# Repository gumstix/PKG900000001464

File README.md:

# Gumstix Raspberry Pi CM4 UprevAI
## PKG900000001464 ![][thumbnail]

The **Gumstix Raspberry Pi CM4 UprevAI** replaces the CM3 compute module on compatible carrier boards, adding a CM4 connector and Google Coral TPU chip.
Accelerate your hardware and migrate it into the field of **Edge AI** without revising your design.

__Features Include__:
* Raspberry Pi CM3 compatible SODIMM edge connection
* Power indicator LED
* Google Coral G313-06329-00 TPU

__Links:__
* [AutoDoc Datasheet][autodoc]
* [Specifications][spec]
* [Store Page][store]
* [Schematics and Layout][hardware]

[thumbnail]: https://d3iwea566ns1n1.cloudfront.net/images/product/40edad650346ab020427c20a98565f45689e575a.png
[autodoc]: PKG900000001464_AutoDoc.pdf
[spec]: PKG900000001464_SpecSheet.pdf
[store]: https://store.gumstix.com/cm4-uprev-ai/
[hardware]: hardware/hardware.md
[firmware]: firmware/firmware.md

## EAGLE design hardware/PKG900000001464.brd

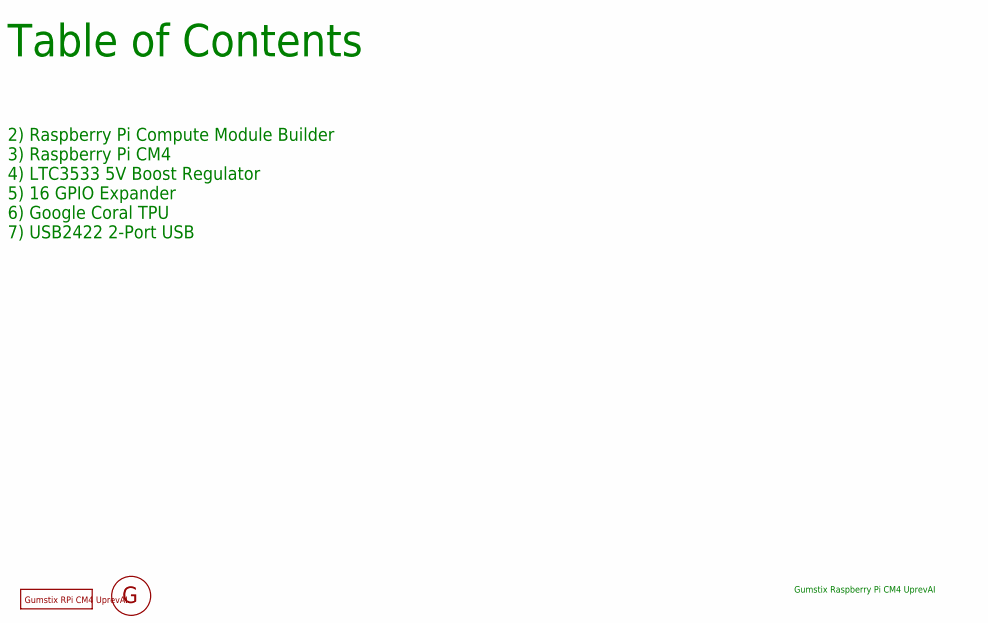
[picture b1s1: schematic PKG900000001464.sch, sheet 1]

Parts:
FD1, FD2, FD3, FD4, FD5, FD6: DNP; FIDUCIAL
U$3: DNP; GEPPETTO_LABEL
U$4: DNP; GEPPETTO_LOGO_SILK10

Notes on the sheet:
Table of Contents
Gumstix Raspberry Pi CM4 UprevAI
2) Raspberry Pi Compute Module Builder
3) Raspberry Pi CM4
4) LTC3533 5V Boost Regulator
5) 16 GPIO Expander
6) Google Coral TPU
7) USB2422 2-Port USB

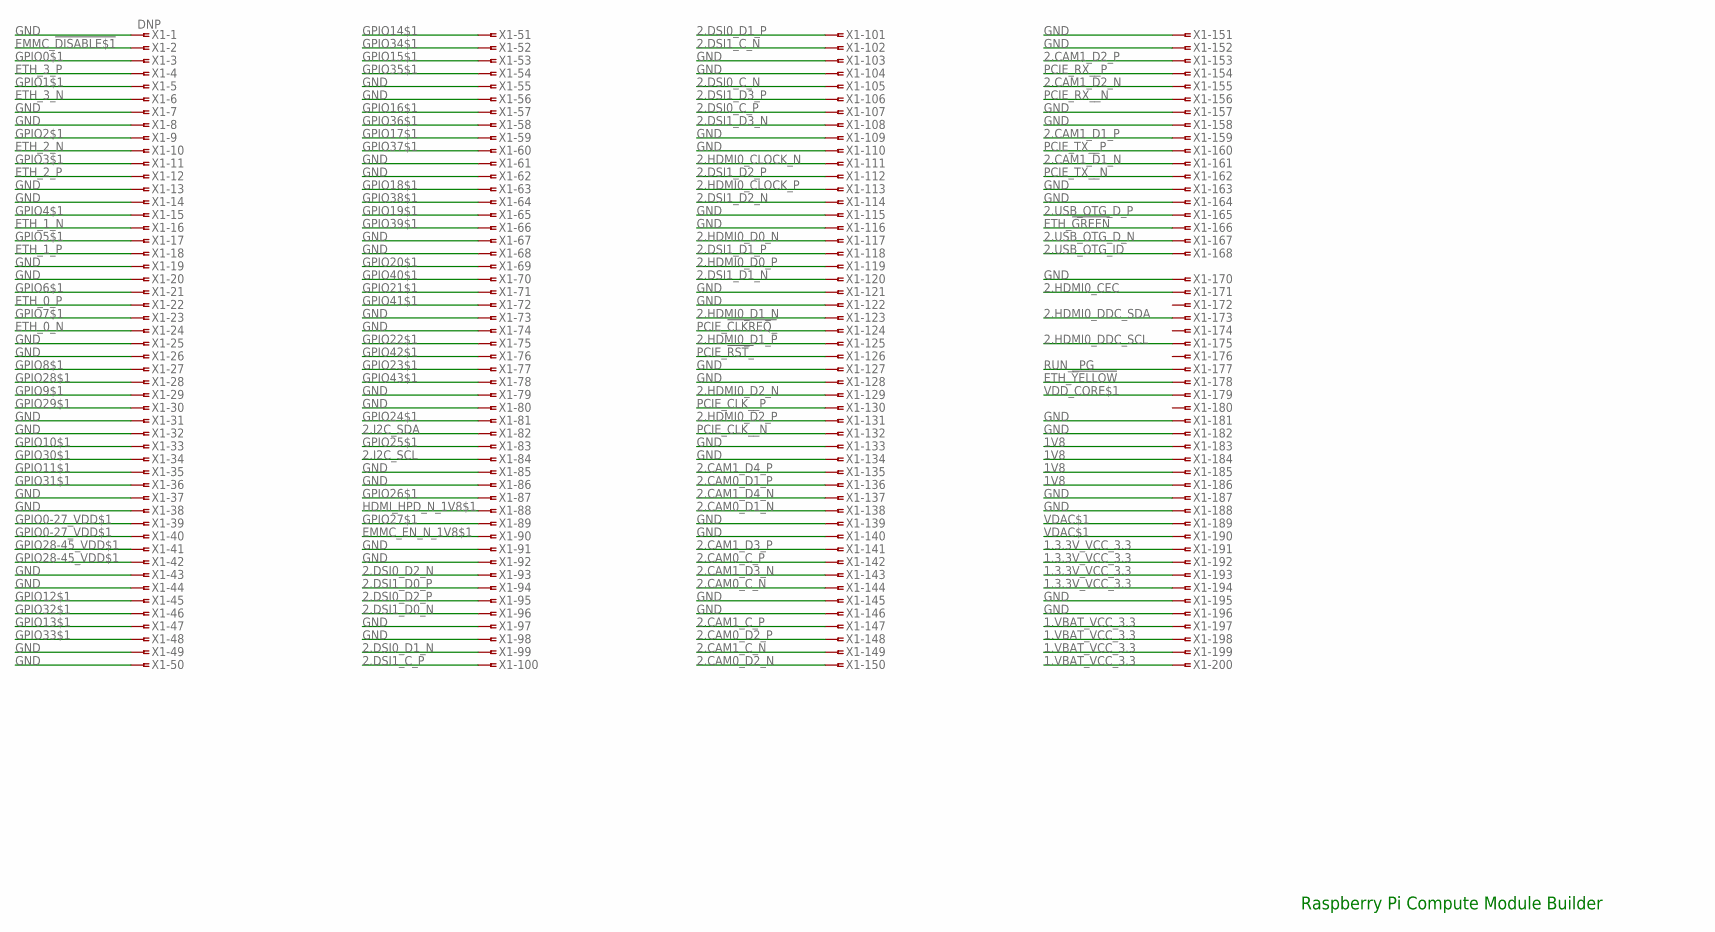
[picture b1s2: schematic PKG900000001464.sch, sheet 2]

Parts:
X1: DNP; SLOT-1376408-1_1.8V_MOD

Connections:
1.3.3V_VCC_3.3: X1.191, X1.192, X1.193, X1.194; also elsewhere on the board
1.VBAT_VCC_3.3: X1.197, X1.198, X1.199, X1.200; also elsewhere on the board
1V8: X1.183, X1.184, X1.185, X1.186
2.CAM0_C_N: X1.144; also elsewhere on the board
2.CAM0_C_P: X1.142; also elsewhere on the board
2.CAM0_D1_N: X1.138; also elsewhere on the board
2.CAM0_D1_P: X1.136; also elsewhere on the board
2.CAM0_D2_N: X1.150; also elsewhere on the board
2.CAM0_D2_P: X1.148; also elsewhere on the board
2.CAM1_C_N: X1.149; also elsewhere on the board
2.CAM1_C_P: X1.147; also elsewhere on the board
2.CAM1_D1_N: X1.161; also elsewhere on the board
2.CAM1_D1_P: X1.159; also elsewhere on the board
2.CAM1_D2_N: X1.155; also elsewhere on the board
2.CAM1_D2_P: X1.153; also elsewhere on the board
2.CAM1_D3_N: X1.143; also elsewhere on the board
2.CAM1_D3_P: X1.141; also elsewhere on the board
2.CAM1_D4_N: X1.137; also elsewhere on the board
2.CAM1_D4_P: X1.135; also elsewhere on the board
2.DSI0_C_N: X1.105; also elsewhere on the board
2.DSI0_C_P: X1.107; also elsewhere on the board
2.DSI0_D1_N: X1.99; also elsewhere on the board
2.DSI0_D1_P: X1.101; also elsewhere on the board
2.DSI0_D2_N: X1.93; also elsewhere on the board
2.DSI0_D2_P: X1.95; also elsewhere on the board
2.DSI1_C_N: X1.102; also elsewhere on the board
2.DSI1_C_P: X1.100; also elsewhere on the board
2.DSI1_D0_N: X1.96; also elsewhere on the board
2.DSI1_D0_P: X1.94; also elsewhere on the board
2.DSI1_D1_N: X1.120; also elsewhere on the board
2.DSI1_D1_P: X1.118; also elsewhere on the board
2.DSI1_D2_N: X1.114; also elsewhere on the board
2.DSI1_D2_P: X1.112; also elsewhere on the board
2.DSI1_D3_N: X1.108; also elsewhere on the board
2.DSI1_D3_P: X1.106; also elsewhere on the board
2.HDMI0_CEC: X1.171; also elsewhere on the board
2.HDMI0_CLOCK_N: X1.111; also elsewhere on the board
2.HDMI0_CLOCK_P: X1.113; also elsewhere on the board
2.HDMI0_D0_N: X1.117; also elsewhere on the board
2.HDMI0_D0_P: X1.119; also elsewhere on the board
2.HDMI0_D1_N: X1.123; also elsewhere on the board
2.HDMI0_D1_P: X1.125; also elsewhere on the board
2.HDMI0_D2_N: X1.129; also elsewhere on the board
2.HDMI0_D2_P: X1.131; also elsewhere on the board
2.HDMI0_DDC_SCL: X1.175; also elsewhere on the board
2.HDMI0_DDC_SDA: X1.173; also elsewhere on the board
2.I2C_SCL: X1.84; also elsewhere on the board
2.I2C_SDA: X1.82; also elsewhere on the board
2.USB_OTG_D_N: X1.167; also elsewhere on the board
2.USB_OTG_D_P: X1.165; also elsewhere on the board
2.USB_OTG_ID: X1.168; also elsewhere on the board
EMMC_!DISABLE$1: X1.2; also elsewhere on the board
EMMC_EN_N_1V8$1: X1.90
ETH_0_N: X1.24; also elsewhere on the board
ETH_0_P: X1.22; also elsewhere on the board
ETH_1_N: X1.16; also elsewhere on the board
ETH_1_P: X1.18; also elsewhere on the board
ETH_2_N: X1.10; also elsewhere on the board
ETH_2_P: X1.12; also elsewhere on the board
ETH_3_N: X1.6; also elsewhere on the board
ETH_3_P: X1.4; also elsewhere on the board
ETH_!GREEN: X1.166; also elsewhere on the board
ETH_!YELLOW: X1.178; also elsewhere on the board
GND: X1.1, X1.7, X1.8, X1.13, X1.14, X1.19, X1.20, X1.25, X1.26, X1.31, X1.32, X1.37, X1.38, X1.43, X1.44, X1.49, X1.50, X1.55, X1.56, X1.61, X1.62, X1.67, X1.68, X1.73, X1.74, X1.79, X1.80, X1.85, X1.86, X1.91, X1.92, X1.97, X1.98, X1.103, X1.104, X1.109, X1.110, X1.115, X1.116, X1.121, X1.122, X1.127, X1.128, X1.133, X1.134, X1.139, X1.140, X1.145, X1.146, X1.151, X1.152, X1.157, X1.158, X1.163, X1.164, X1.170, X1.181, X1.182, X1.187, X1.188, X1.195, X1.196; also elsewhere on the board
GPIO0$1: X1.3; also elsewhere on the board
GPIO0-27_VDD$1: X1.39, X1.40
GPIO1$1: X1.5; also elsewhere on the board
GPIO2$1: X1.9; also elsewhere on the board
GPIO3$1: X1.11; also elsewhere on the board
GPIO4$1: X1.15; also elsewhere on the board
GPIO5$1: X1.17; also elsewhere on the board
GPIO6$1: X1.21; also elsewhere on the board
GPIO7$1: X1.23; also elsewhere on the board
GPIO8$1: X1.27; also elsewhere on the board
GPIO9$1: X1.29; also elsewhere on the board
GPIO10$1: X1.33; also elsewhere on the board
GPIO11$1: X1.35; also elsewhere on the board
GPIO12$1: X1.45; also elsewhere on the board
GPIO13$1: X1.47; also elsewhere on the board
GPIO14$1: X1.51; also elsewhere on the board
GPIO15$1: X1.53; also elsewhere on the board
GPIO16$1: X1.57; also elsewhere on the board
GPIO17$1: X1.59; also elsewhere on the board
GPIO18$1: X1.63; also elsewhere on the board
GPIO19$1: X1.65; also elsewhere on the board
GPIO20$1: X1.69; also elsewhere on the board
GPIO21$1: X1.71; also elsewhere on the board
GPIO22$1: X1.75; also elsewhere on the board
GPIO23$1: X1.77; also elsewhere on the board
GPIO24$1: X1.81; also elsewhere on the board
GPIO25$1: X1.83; also elsewhere on the board
GPIO26$1: X1.87; also elsewhere on the board
GPIO27$1: X1.89; also elsewhere on the board
GPIO28$1: X1.28; also elsewhere on the board
GPIO28-45_VDD$1: X1.41, X1.42
GPIO29$1: X1.30; also elsewhere on the board
GPIO30$1: X1.34; also elsewhere on the board
GPIO31$1: X1.36; also elsewhere on the board
GPIO32$1: X1.46; also elsewhere on the board
GPIO33$1: X1.48; also elsewhere on the board
GPIO34$1: X1.52; also elsewhere on the board
GPIO35$1: X1.54; also elsewhere on the board
GPIO36$1: X1.58; also elsewhere on the board
GPIO37$1: X1.60; also elsewhere on the board
GPIO38$1: X1.64; also elsewhere on the board
GPIO39$1: X1.66; also elsewhere on the board
GPIO40$1: X1.70; also elsewhere on the board
GPIO41$1: X1.72; also elsewhere on the board
GPIO42$1: X1.76; also elsewhere on the board
GPIO43$1: X1.78; also elsewhere on the board
HDMI_HPD_N_1V8$1: X1.88; also elsewhere on the board
PCIE_!CLKREQ_: X1.124
PCIE_!RST_: X1.126
PCIE_CLK__N: X1.132
PCIE_CLK__P: X1.130
PCIE_RX__N: X1.156
PCIE_RX__P: X1.154
PCIE_TX__N: X1.162
PCIE_TX__P: X1.160
RUN__PG: X1.177; also elsewhere on the board
VDAC$1: X1.189, X1.190
VDD_CORE$1: X1.179

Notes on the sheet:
Raspberry Pi Compute Module Builder

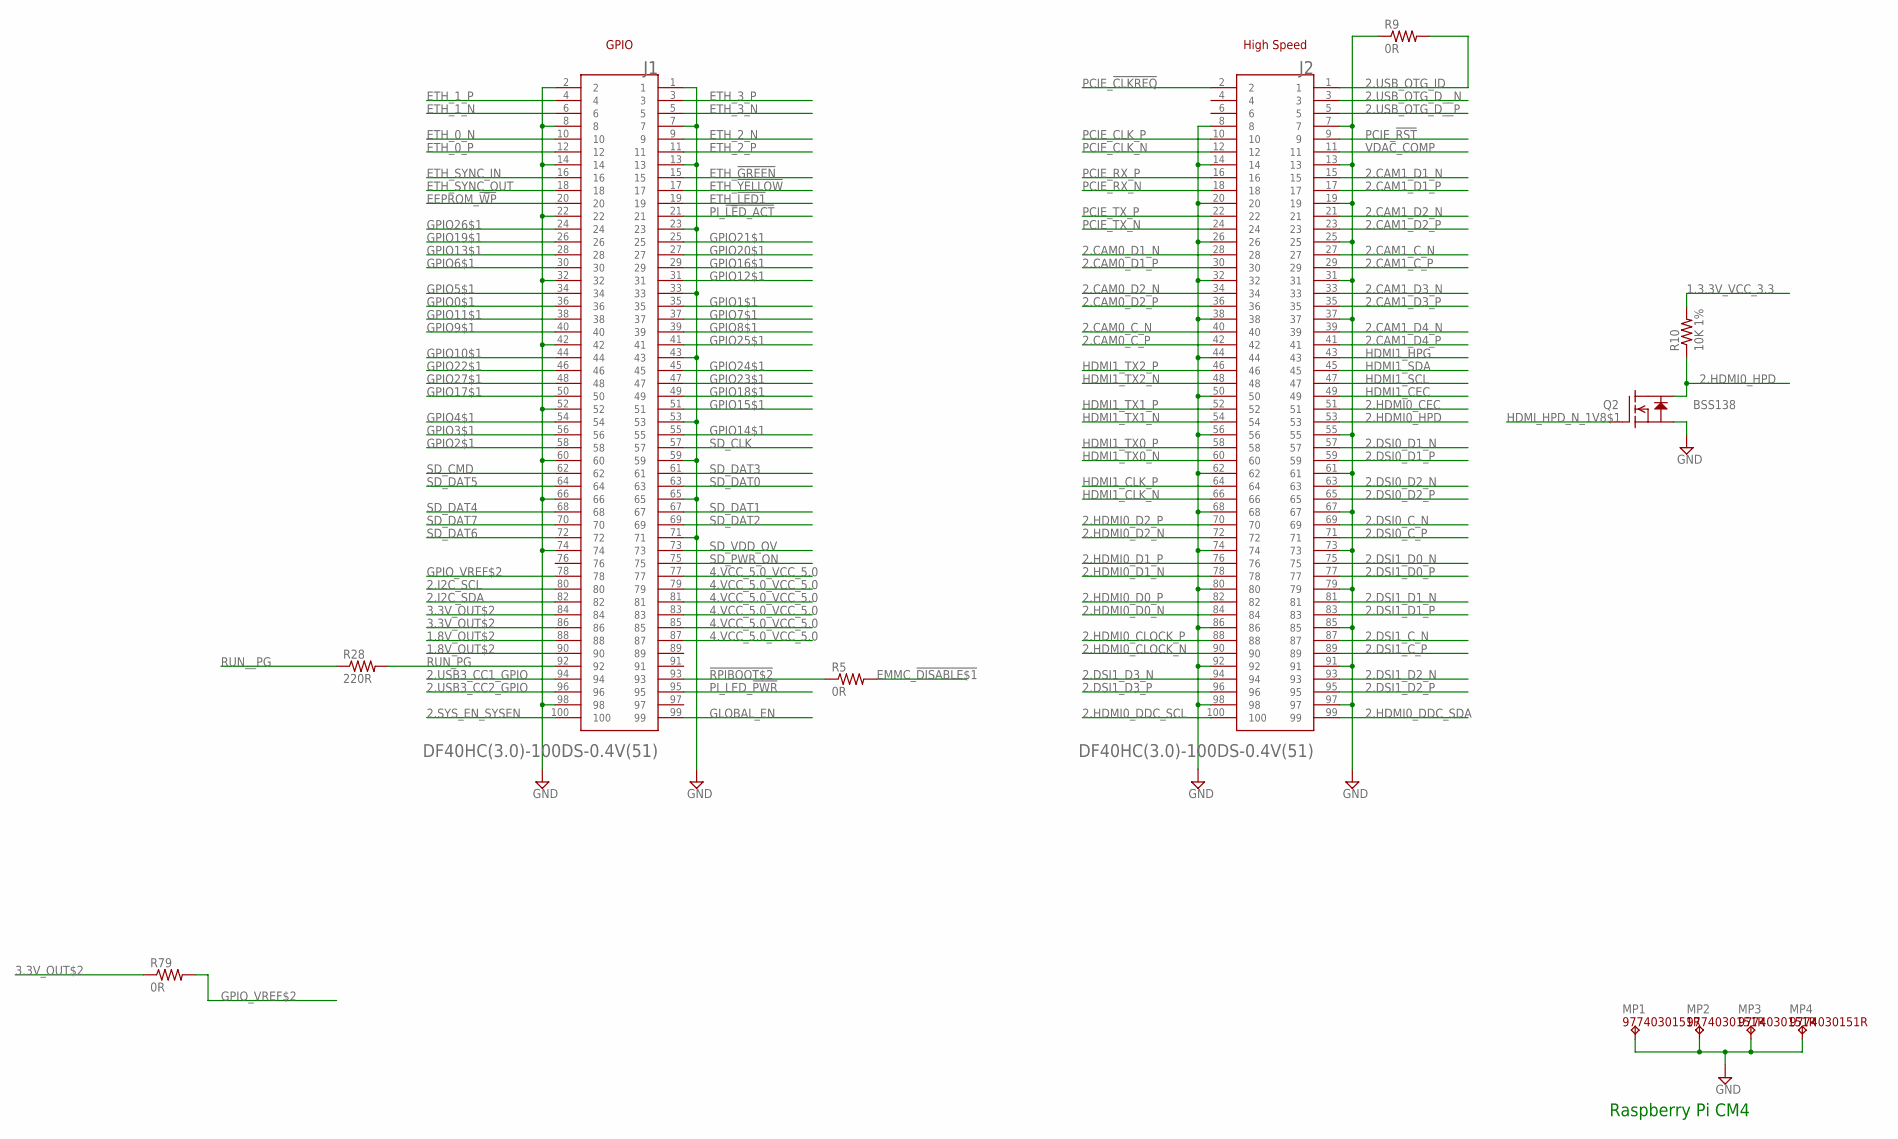
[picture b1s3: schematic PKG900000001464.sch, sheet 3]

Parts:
J1, J2: DF40HC(3.0)-100DS-0.4V(51); HRS_DF40C-100DS-0.4V(51)
MP1, MP2, MP3, MP4: 9774030151R; WA-SMSI_9774___151
Q2: BSS138; SOT23
R5, R9, R79: 0R; 0201
R10: 10K 1%; 0201
R28: 220R; 0402

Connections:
1.3.3V_VCC_3.3: R10.2; also elsewhere on the board
1.8V_OUT$2: J1.88, J1.90
2.CAM0_C_N: J2.40; also elsewhere on the board
2.CAM0_C_P: J2.42; also elsewhere on the board
2.CAM0_D1_N: J2.28; also elsewhere on the board
2.CAM0_D1_P: J2.30; also elsewhere on the board
2.CAM0_D2_N: J2.34; also elsewhere on the board
2.CAM0_D2_P: J2.36; also elsewhere on the board
2.CAM1_C_N: J2.27; also elsewhere on the board
2.CAM1_C_P: J2.29; also elsewhere on the board
2.CAM1_D1_N: J2.15; also elsewhere on the board
2.CAM1_D1_P: J2.17; also elsewhere on the board
2.CAM1_D2_N: J2.21; also elsewhere on the board
2.CAM1_D2_P: J2.23; also elsewhere on the board
2.CAM1_D3_N: J2.33; also elsewhere on the board
2.CAM1_D3_P: J2.35; also elsewhere on the board
2.CAM1_D4_N: J2.39; also elsewhere on the board
2.CAM1_D4_P: J2.41; also elsewhere on the board
2.DSI0_C_N: J2.69; also elsewhere on the board
2.DSI0_C_P: J2.71; also elsewhere on the board
2.DSI0_D1_N: J2.57; also elsewhere on the board
2.DSI0_D1_P: J2.59; also elsewhere on the board
2.DSI0_D2_N: J2.63; also elsewhere on the board
2.DSI0_D2_P: J2.65; also elsewhere on the board
2.DSI1_C_N: J2.87; also elsewhere on the board
2.DSI1_C_P: J2.89; also elsewhere on the board
2.DSI1_D0_N: J2.75; also elsewhere on the board
2.DSI1_D0_P: J2.77; also elsewhere on the board
2.DSI1_D1_N: J2.81; also elsewhere on the board
2.DSI1_D1_P: J2.83; also elsewhere on the board
2.DSI1_D2_N: J2.93; also elsewhere on the board
2.DSI1_D2_P: J2.95; also elsewhere on the board
2.DSI1_D3_N: J2.94; also elsewhere on the board
2.DSI1_D3_P: J2.96; also elsewhere on the board
2.HDMI0_CEC: J2.51; also elsewhere on the board
2.HDMI0_CLOCK_N: J2.90; also elsewhere on the board
2.HDMI0_CLOCK_P: J2.88; also elsewhere on the board
2.HDMI0_D0_N: J2.84; also elsewhere on the board
2.HDMI0_D0_P: J2.82; also elsewhere on the board
2.HDMI0_D1_N: J2.78; also elsewhere on the board
2.HDMI0_D1_P: J2.76; also elsewhere on the board
2.HDMI0_D2_N: J2.72; also elsewhere on the board
2.HDMI0_D2_P: J2.70; also elsewhere on the board
2.HDMI0_DDC_SCL: J2.100; also elsewhere on the board
2.HDMI0_DDC_SDA: J2.99; also elsewhere on the board
2.HDMI0_HPD: J2.53, Q2.3 (D), R10.1
2.I2C_SCL: J1.80; also elsewhere on the board
2.I2C_SDA: J1.82; also elsewhere on the board
2.SYS_EN_SYSEN: J1.100
2.USB3_CC1_GPIO: J1.94
2.USB3_CC2_GPIO: J1.96
2.USB_OTG_D__N: J2.3; also elsewhere on the board
2.USB_OTG_D__P: J2.5; also elsewhere on the board
2.USB_OTG_ID: J2.1, R9.2; also elsewhere on the board
3.3V_OUT$2: J1.84, J1.86, R79.1; also elsewhere on the board
4.VCC_5.0_VCC_5.0: J1.77, J1.79, J1.81, J1.83, J1.85, J1.87; also elsewhere on the board
!RPIBOOT$2: J1.93, R5.1
EEPROM_!WP: J1.20
EMMC_!DISABLE$1: R5.2; also elsewhere on the board
ETH_0_N: J1.10; also elsewhere on the board
ETH_0_P: J1.12; also elsewhere on the board
ETH_1_N: J1.6; also elsewhere on the board
ETH_1_P: J1.4; also elsewhere on the board
ETH_2_N: J1.9; also elsewhere on the board
ETH_2_P: J1.11; also elsewhere on the board
ETH_3_N: J1.5; also elsewhere on the board
ETH_3_P: J1.3; also elsewhere on the board
ETH_!GREEN: J1.15; also elsewhere on the board
ETH_!LED1: J1.19
ETH_!YELLOW: J1.17; also elsewhere on the board
ETH_SYNC_IN: J1.16
ETH_SYNC_OUT: J1.18
GLOBAL_EN: J1.99
GND: J1.1, J1.2, J1.7, J1.8, J1.13, J1.14, J1.22, J1.23, J1.32, J1.33, J1.42, J1.43, J1.52, J1.53, J1.59, J1.60, J1.65, J1.66, J1.71, J1.74, J1.98, J2.7, J2.8, J2.13, J2.14, J2.19, J2.20, J2.25, J2.26, J2.31, J2.32, J2.37, J2.38, J2.44, J2.50, J2.55, J2.56, J2.61, J2.62, J2.67, J2.68, J2.73, J2.74, J2.79, J2.80, J2.85, J2.86, J2.91, J2.92, J2.97, J2.98, MP1.1, MP2.1, MP3.1, MP4.1, Q2.2 (S), R9.1; also elsewhere on the board
GPIO0$1: J1.36; also elsewhere on the board
GPIO1$1: J1.35; also elsewhere on the board
GPIO2$1: J1.58; also elsewhere on the board
GPIO3$1: J1.56; also elsewhere on the board
GPIO4$1: J1.54; also elsewhere on the board
GPIO5$1: J1.34; also elsewhere on the board
GPIO6$1: J1.30; also elsewhere on the board
GPIO7$1: J1.37; also elsewhere on the board
GPIO8$1: J1.39; also elsewhere on the board
GPIO9$1: J1.40; also elsewhere on the board
GPIO10$1: J1.44; also elsewhere on the board
GPIO11$1: J1.38; also elsewhere on the board
GPIO12$1: J1.31; also elsewhere on the board
GPIO13$1: J1.28; also elsewhere on the board
GPIO14$1: J1.55; also elsewhere on the board
GPIO15$1: J1.51; also elsewhere on the board
GPIO16$1: J1.29; also elsewhere on the board
GPIO17$1: J1.50; also elsewhere on the board
GPIO18$1: J1.49; also elsewhere on the board
GPIO19$1: J1.26; also elsewhere on the board
GPIO20$1: J1.27; also elsewhere on the board
GPIO21$1: J1.25; also elsewhere on the board
GPIO22$1: J1.46; also elsewhere on the board
GPIO23$1: J1.47; also elsewhere on the board
GPIO24$1: J1.45; also elsewhere on the board
GPIO25$1: J1.41; also elsewhere on the board
GPIO26$1: J1.24; also elsewhere on the board
GPIO27$1: J1.48; also elsewhere on the board
GPIO_VREF$2: J1.78, R79.2
HDMI1_CEC: J2.49
HDMI1_CLK_N: J2.66
HDMI1_CLK_P: J2.64
HDMI1_HPG: J2.43
HDMI1_SCL: J2.47
HDMI1_SDA: J2.45
HDMI1_TX0_N: J2.60
HDMI1_TX0_P: J2.58
HDMI1_TX1_N: J2.54
HDMI1_TX1_P: J2.52
HDMI1_TX2_N: J2.48
HDMI1_TX2_P: J2.46
HDMI_HPD_N_1V8$1: Q2.1 (G); also elsewhere on the board
PCIE_!CLKREQ: J2.2; also elsewhere on the board
PCIE_!RST: J2.9
PCIE_CLK_N: J2.12; also elsewhere on the board
PCIE_CLK_P: J2.10; also elsewhere on the board
PCIE_RX_N: J2.18; also elsewhere on the board
PCIE_RX_P: J2.16; also elsewhere on the board
PCIE_TX_N: J2.24; also elsewhere on the board
PCIE_TX_P: J2.22; also elsewhere on the board
PI_!LED_ACT: J1.21
PI_LED_!PWR: J1.95
RUN_PG: J1.92, R28.2; also elsewhere on the board
RUN__PG: R28.1; also elsewhere on the board
SD_CLK: J1.57
SD_CMD: J1.62
SD_DAT0: J1.63
SD_DAT1: J1.67
SD_DAT2: J1.69
SD_DAT3: J1.61
SD_DAT4: J1.68
SD_DAT5: J1.64
SD_DAT6: J1.72
SD_DAT7: J1.70
SD_PWR_ON: J1.75
SD_VDD_OV: J1.73
VDAC_COMP: J2.11

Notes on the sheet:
Raspberry Pi CM4
GPIO
High Speed

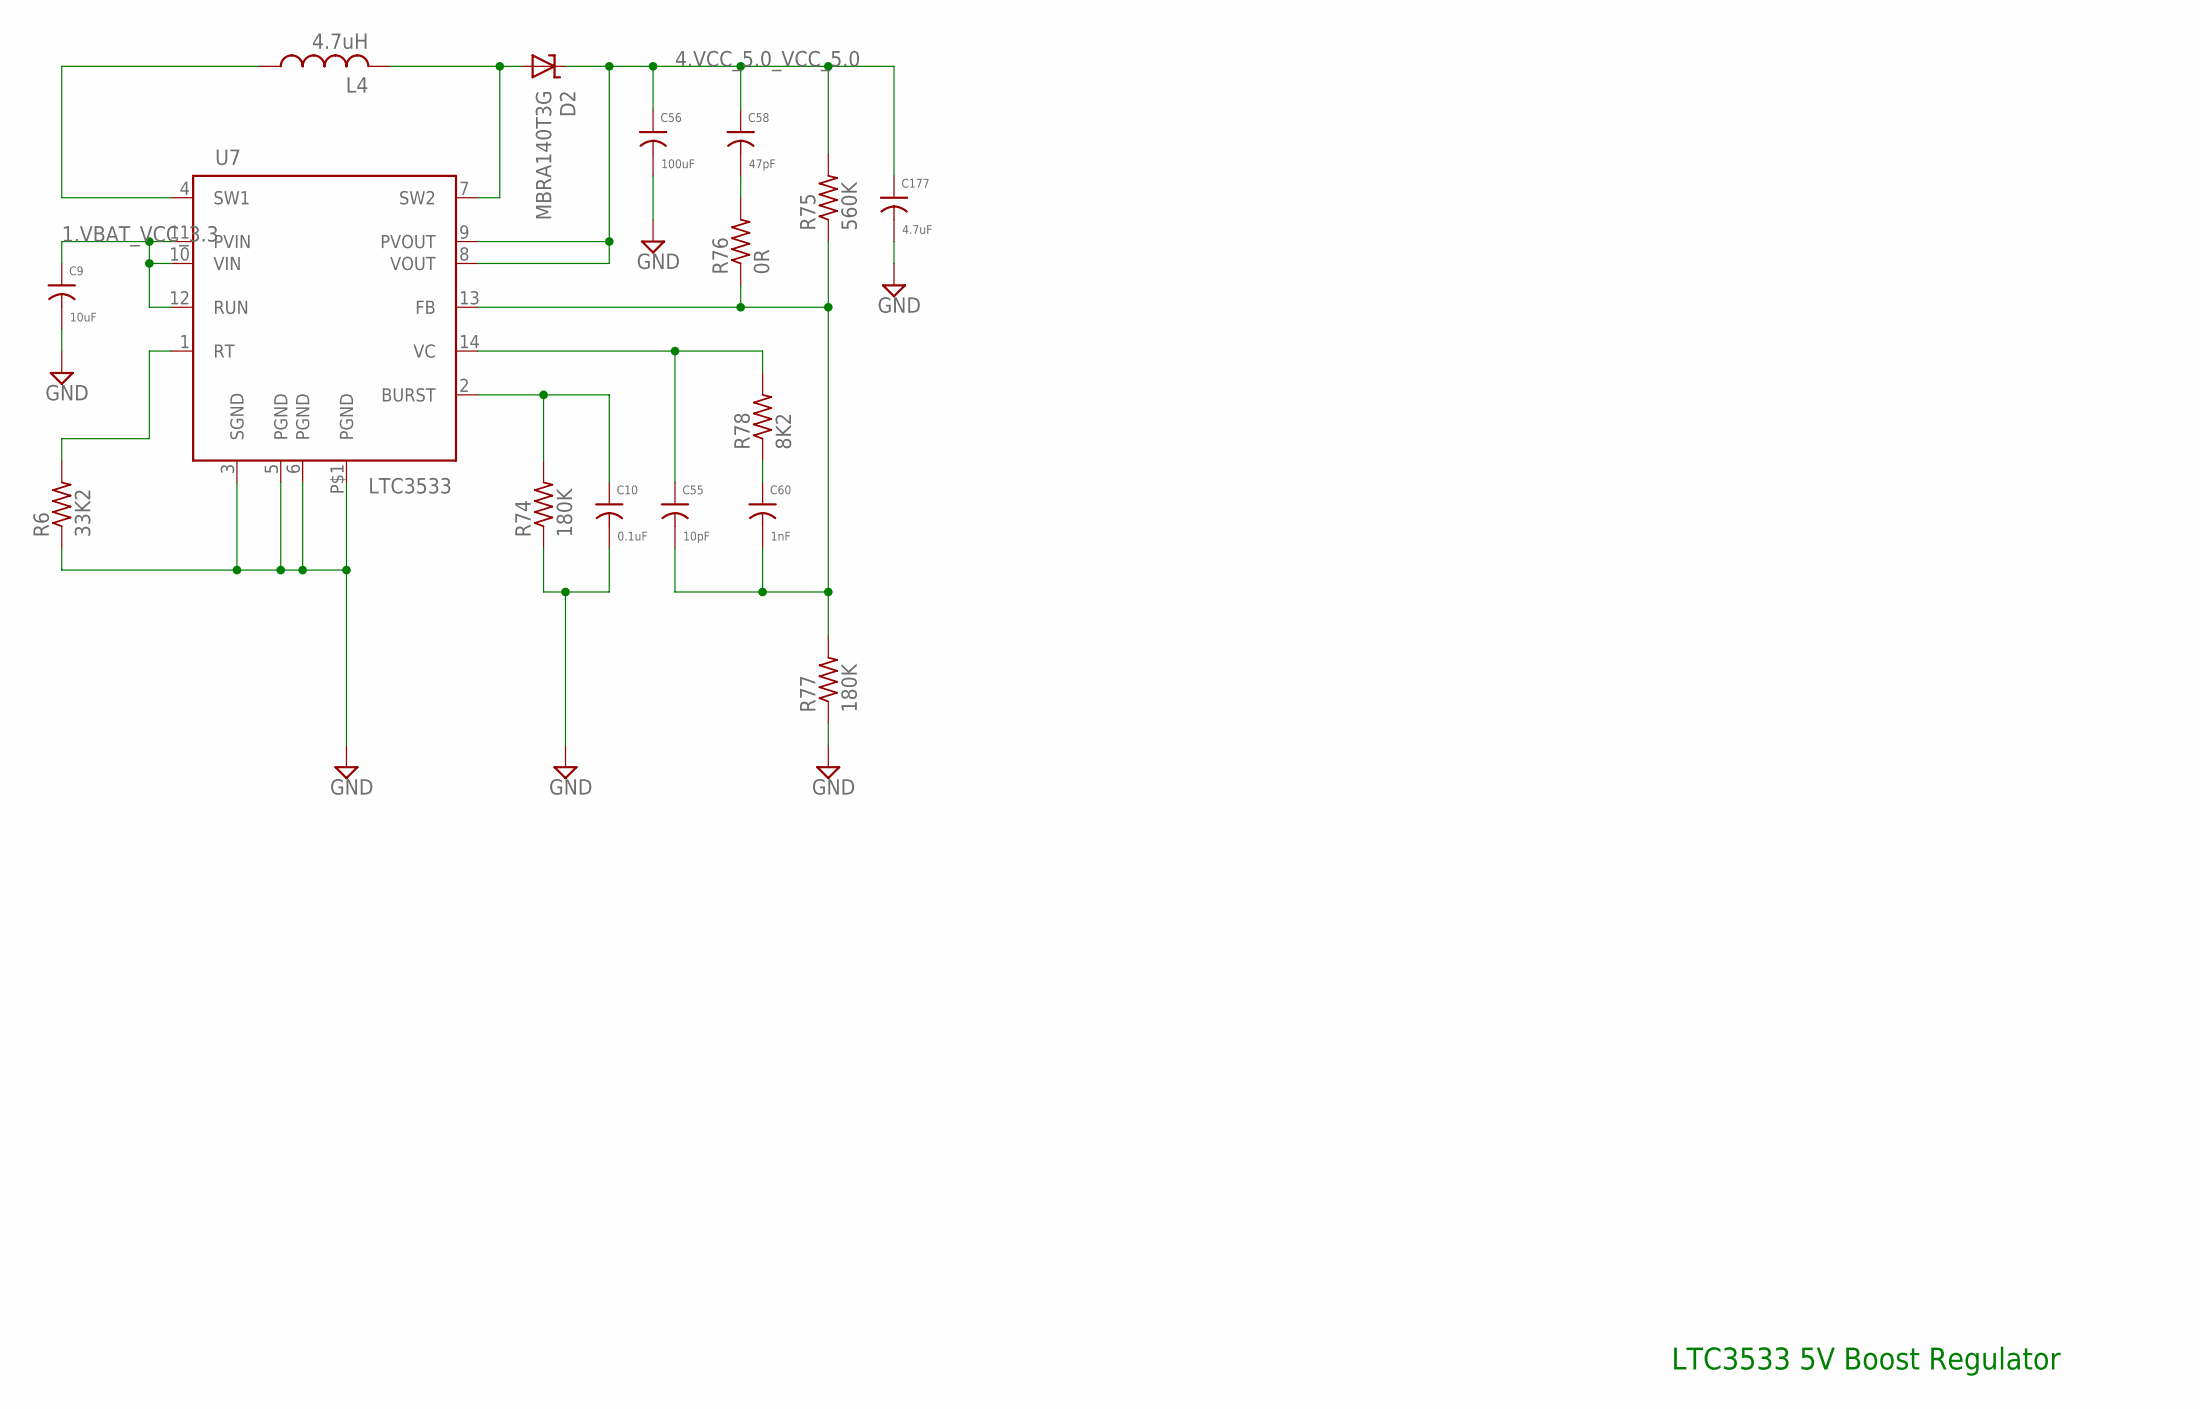
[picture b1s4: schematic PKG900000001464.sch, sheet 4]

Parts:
C9: 10uF; 0603
C10: 0.1uF; 0201
C55: 10pF; 0201
C56: 100uF; 1206
C58: 47pF; 0201
C60: 1nF; 0402
C177: 4.7uF; 0603
D2: MBRA140T3G; SMAJ
L4: 4.7uH; B82462
R6: 33K2; 0402
R74, R77: 180K; 0201
R75: 560K; 0402
R76: 0R; 0201
R78: 8K2; 0402
U7: LTC3533; DFN-14

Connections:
1.VBAT_VCC_3.3: C9.1, U7.10 (VIN), U7.11 (PVIN), U7.12 (RUN); also elsewhere on the board
4.VCC_5.0_VCC_5.0: C56.1, C58.1, C177.1, D2.C, R75.2, U7.8 (VOUT), U7.9 (PVOUT); also elsewhere on the board
BURST$3: C10.1, R74.2, U7.2 (BURST)
FB_5$3: C55.2, C60.2, R75.1, R76.1, R77.2, U7.13 (FB)
FB_5A$3: C58.2, R76.2
GND: C9.2, C10.2, C56.2, C177.2, R6.1, R74.1, R77.1, U7.3 (SGND), U7.5 (PGND), U7.6 (PGND), U7.P$1 (PGND); also elsewhere on the board
PRE_FB$3: C60.1, R78.1
RT$3: R6.2, U7.1 (RT)
SW1$3: L4.1, U7.4 (SW1)
SW2$3: D2.A, L4.2, U7.7 (SW2)
VC$3: C55.1, R78.2, U7.14 (VC)

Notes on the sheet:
LTC3533 5V Boost Regulator

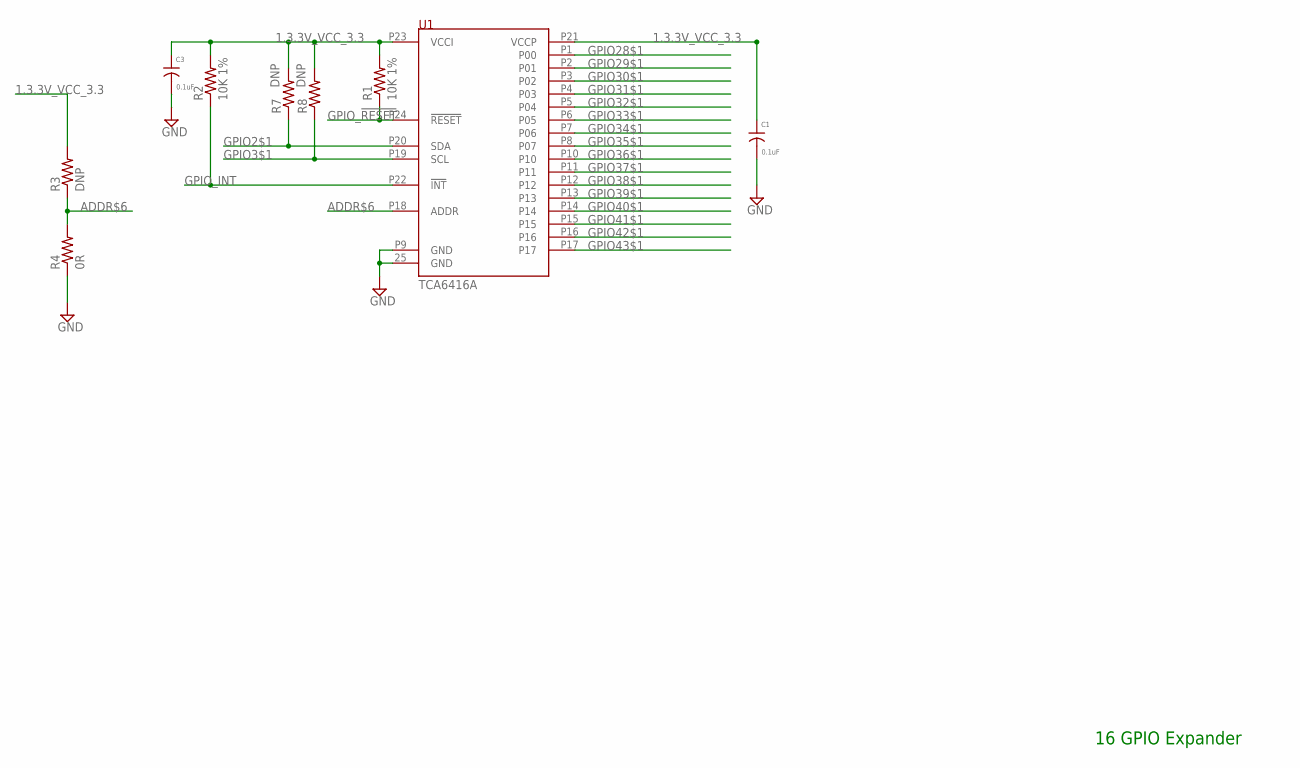
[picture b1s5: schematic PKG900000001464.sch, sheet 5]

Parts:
C1, C3: 0.1uF; 0201
R1, R2: 10K 1%; 0201
R3, R7, R8: DNP; 0201
R4: 0R; 0201
U1: TCA6416A; WQFN24

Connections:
1.3.3V_VCC_3.3: C1.1, C3.1, R1.2, R2.2, R3.2, R7.2, R8.2, U1.P21 (VCCP), U1.P23 (VCCI); also elsewhere on the board
ADDR$6: R3.1, R4.2, U1.P18 (ADDR)
GND: C1.2, C3.2, R4.1, U1.25 (GND), U1.P9 (GND); also elsewhere on the board
GPIO2$1: R7.1, U1.P20 (SDA); also elsewhere on the board
GPIO3$1: R8.1, U1.P19 (SCL); also elsewhere on the board
GPIO28$1: U1.P1 (P00); also elsewhere on the board
GPIO29$1: U1.P2 (P01); also elsewhere on the board
GPIO30$1: U1.P3 (P02); also elsewhere on the board
GPIO31$1: U1.P4 (P03); also elsewhere on the board
GPIO32$1: U1.P5 (P04); also elsewhere on the board
GPIO33$1: U1.P6 (P05); also elsewhere on the board
GPIO34$1: U1.P7 (P06); also elsewhere on the board
GPIO35$1: U1.P8 (P07); also elsewhere on the board
GPIO36$1: U1.P10; also elsewhere on the board
GPIO37$1: U1.P11; also elsewhere on the board
GPIO38$1: U1.P12; also elsewhere on the board
GPIO39$1: U1.P13; also elsewhere on the board
GPIO40$1: U1.P14; also elsewhere on the board
GPIO41$1: U1.P15; also elsewhere on the board
GPIO42$1: U1.P16; also elsewhere on the board
GPIO43$1: U1.P17; also elsewhere on the board
GPIO_!RESET: R1.1, U1.P24 (!RESET!)
GPIO_INT: R2.1, U1.P22 (!INT!)

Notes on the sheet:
16 GPIO Expander

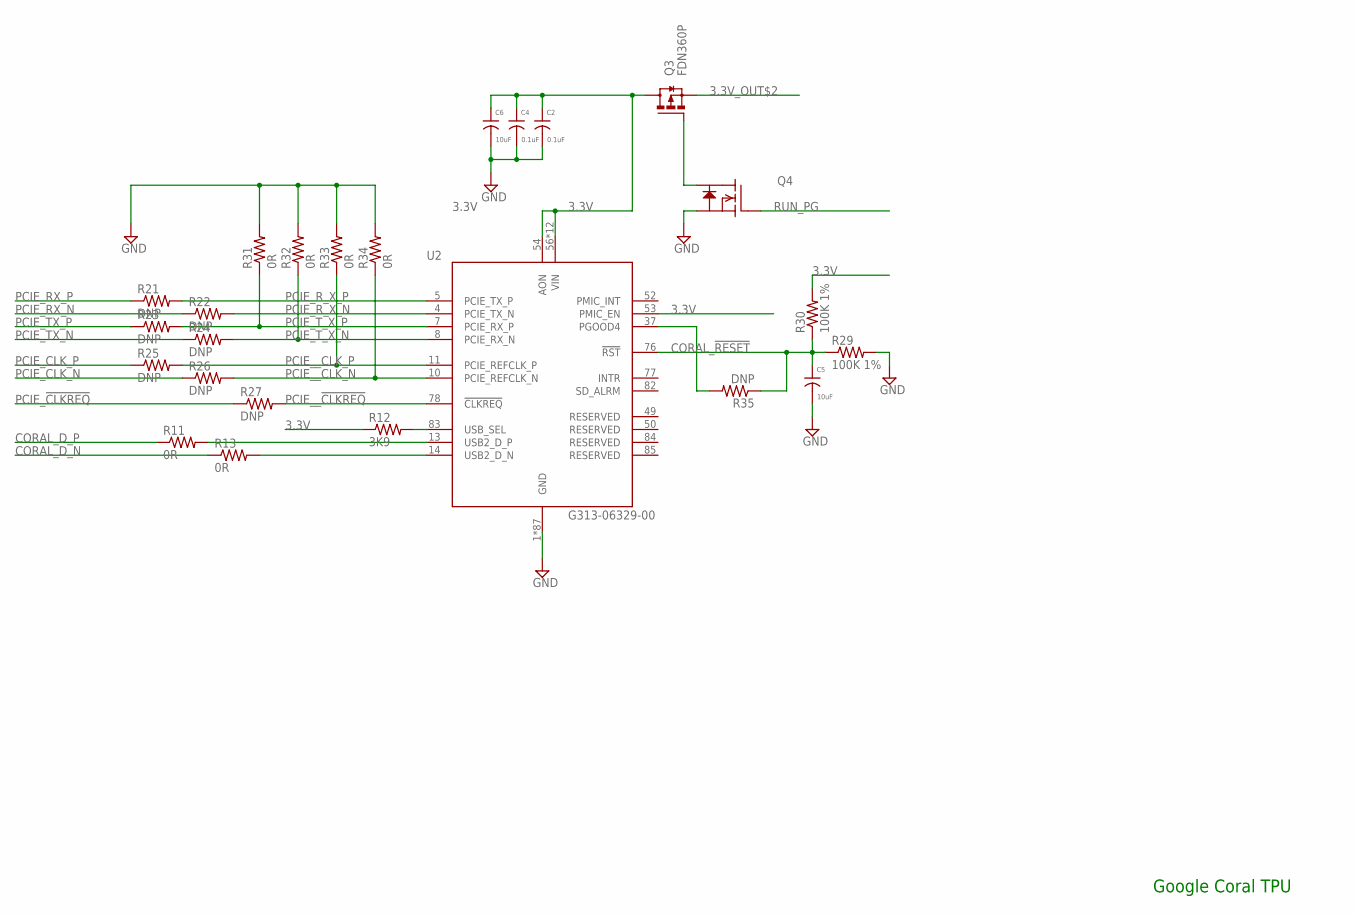
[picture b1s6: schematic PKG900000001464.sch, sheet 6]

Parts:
C2, C4: 0.1uF; 0201
C5, C6: 10uF; 0603
Q3: FDN360P; SOT23
Q4: BSS138; SOT23
R11, R13, R31, R32, R33, R34: 0R; 0201
R12: 3K9; 0201
R21, R22, R23, R24, R25, R26, R27, R35: DNP; 0201
R29, R30: 100K 1%; 0201
U2: G313-06329-00

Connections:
3.3V: C2.1, C4.1, C6.1, Q3.3 (D), R12.1, R30.2, U2.53 (PMIC_EN), U2.54 (AON), U2.56 (VIN), U2.57 (VIN), U2.58 (VIN), U2.59 (VIN), U2.60 (VIN), U2.61 (VIN), U2.62 (VIN), U2.63 (VIN), U2.64 (VIN), U2.65 (VIN), U2.66 (VIN), U2.67 (VIN); also elsewhere on the board
3.3V_OUT$2: Q3.2 (S); also elsewhere on the board
CORAL_!RESET: C5.1, R29.1, R30.1, R35.1, U2.76 (!RST)
CORAL_D_N: R13.1; also elsewhere on the board
CORAL_D_P: R11.1; also elsewhere on the board
CORAL_USB_SELECT: R12.2, U2.83 (USB_SEL)
CORAL__D_N: R13.2, U2.14 (USB2_D_N)
CORAL__D_P: R11.2, U2.13 (USB2_D_P)
FET_ENABLES: Q3.1 (G), Q4.3 (D)
GND: C2.2, C4.2, C5.2, C6.2, Q4.2 (S), R29.2, R31.2, R32.2, R33.2, R34.2, U2.1 (GND), U2.2 (GND), U2.3 (GND), U2.6 (GND), U2.9 (GND), U2.12 (GND), U2.15 (GND), U2.16 (GND), U2.17 (GND), U2.18 (GND), U2.19 (GND), U2.20 (GND), U2.21 (GND), U2.22 (GND), U2.23 (GND), U2.24 (GND), U2.25 (GND), U2.26 (GND), U2.27 (GND), U2.28 (GND), U2.29 (GND), U2.30 (GND), U2.31 (GND), U2.32 (GND), U2.33 (GND), U2.34 (GND), U2.35 (GND), U2.36 (GND), U2.38 (GND), U2.39 (GND), U2.40 (GND), U2.41 (GND), U2.42 (GND), U2.43 (GND), U2.44 (GND), U2.45 (GND), U2.46 (GND), U2.47 (GND), U2.48 (GND), U2.51 (GND), U2.55 (GND), U2.68 (GND), U2.69 (GND), U2.70 (GND), U2.71 (GND), U2.72 (GND), U2.73 (GND), U2.74 (GND), U2.75 (GND), U2.79 (GND), U2.80 (GND), U2.81 (GND), U2.86 (GND), U2.87 (GND), U2.88 (GND), U2.89 (GND), U2.90 (GND), U2.91 (GND), U2.92 (GND), U2.93 (GND), U2.94 (GND), U2.95 (GND), U2.96 (GND), U2.97 (GND), U2.98 (GND), U2.99 (GND), U2.100 (GND), U2.101 (GND), U2.102 (GND), U2.103 (GND), U2.104 (GND), U2.105 (GND), U2.106 (GND), U2.107 (GND), U2.108 (GND), U2.109 (GND), U2.110 (GND), U2.111 (GND), U2.112 (GND), U2.113 (GND), U2.114 (GND), U2.115 (GND), U2.116 (GND), U2.117 (GND), U2.118 (GND), U2.119 (GND), U2.120 (GND); also elsewhere on the board
PCIE_!CLKREQ: R27.1; also elsewhere on the board
PCIE_CLK_N: R26.1; also elsewhere on the board
PCIE_CLK_P: R25.1; also elsewhere on the board
PCIE_RX_N: R22.1; also elsewhere on the board
PCIE_RX_P: R21.1; also elsewhere on the board
PCIE_R_X_N: R22.2, U2.4 (PCIE_TX_N)
PCIE_R_X_P: R21.2, U2.5 (PCIE_TX_P)
PCIE_TX_N: R24.1; also elsewhere on the board
PCIE_TX_P: R23.1; also elsewhere on the board
PCIE_T_X_N: R24.2, R32.1, U2.8 (PCIE_RX_N)
PCIE_T_X_P: R23.2, R31.1, U2.7 (PCIE_RX_P)
PCIE__!CLKREQ: R27.2, U2.78 (!CLKREQ)
PCIE__CLK_N: R26.2, R34.1, U2.10 (PCIE_REFCLK_N)
PCIE__CLK_P: R25.2, R33.1, U2.11 (PCIE_REFCLK_P)
PGOOD4$: R35.2, U2.37 (PGOOD4)
RUN_PG: Q4.1 (G); also elsewhere on the board

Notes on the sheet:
Google Coral TPU

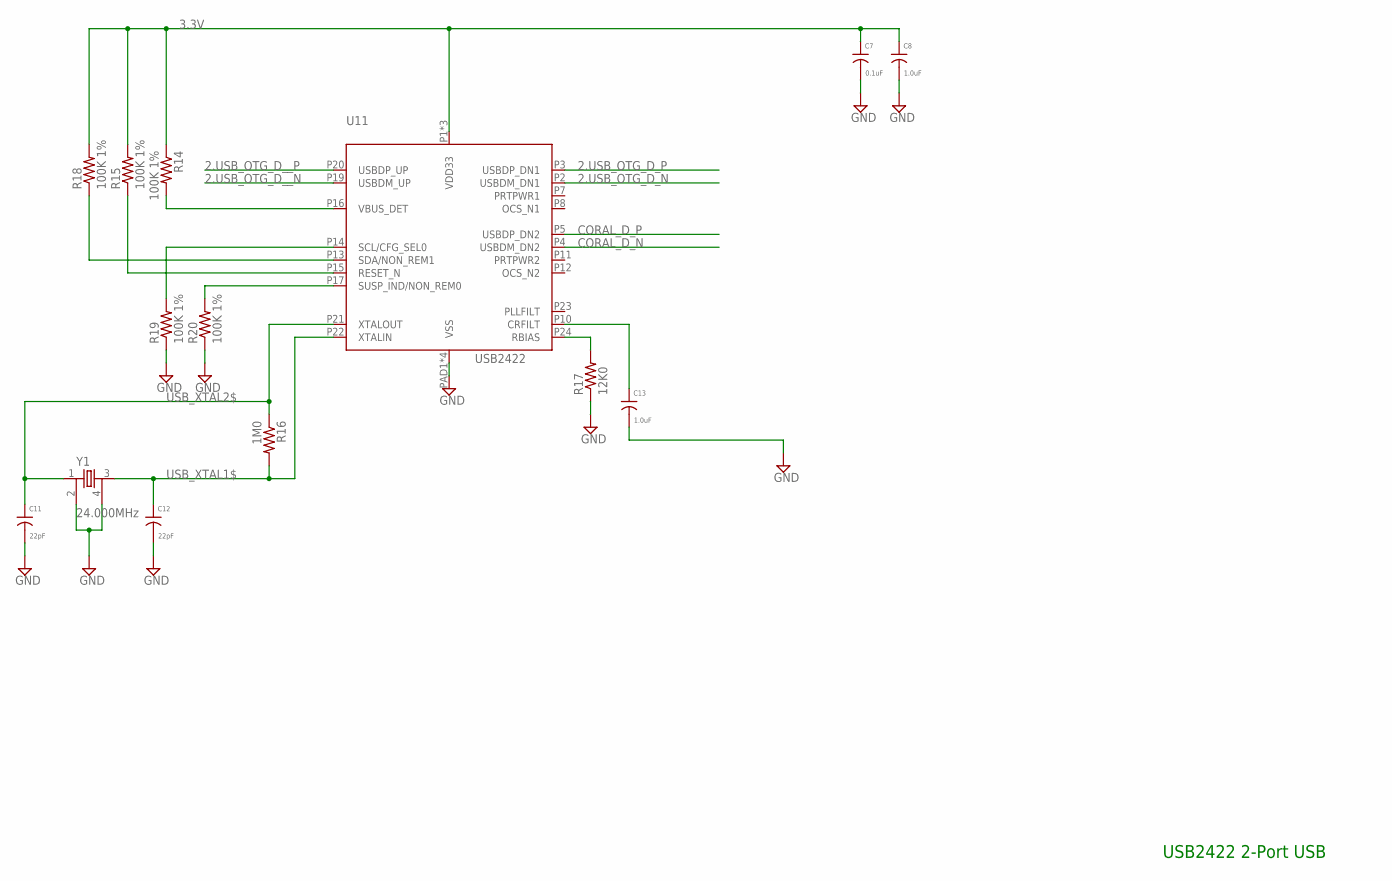
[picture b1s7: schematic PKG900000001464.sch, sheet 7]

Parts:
C7: 0.1uF; 0201
C8, C13: 1.0uF; 0402
C11, C12: 22pF; 0201
R14, R15, R18, R19, R20: 100K 1%; 0201
R16: 1M0; 0201
R17: 12K0; 0201
U11: USB2422; VQFN24
Y1: 24.000MHz; CRYSTAL-3225

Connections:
2.USB_OTG_D_N: U11.P2 (USBDM_DN1); also elsewhere on the board
2.USB_OTG_D_P: U11.P3 (USBDP_DN1); also elsewhere on the board
2.USB_OTG_D__N: U11.P19 (USBDM_UP); also elsewhere on the board
2.USB_OTG_D__P: U11.P20 (USBDP_UP); also elsewhere on the board
3.3V: C7.1, C8.1, R14.1, R15.2, R18.2, U11.P1 (VDD33), U11.P9 (VDD33), U11.P18 (VDD33); also elsewhere on the board
CORAL_D_N: U11.P4 (USBDM_DN2); also elsewhere on the board
CORAL_D_P: U11.P5 (USBDP_DN2); also elsewhere on the board
GND: C7.2, C8.2, C11.2, C12.2, C13.2, R17.1, R19.1, R20.1, U11.PAD1 (VSS), U11.PAD2 (VSS), U11.PAD3 (VSS), U11.PAD4 (VSS), Y1.2, Y1.4; also elsewhere on the board
HUB_CFG_SEL0: R19.2, U11.P14 (SCL/CFG_SEL0)
HUB_NON_REM0: R20.2, U11.P17 (SUSP_IND/NON_REM0)
HUB_NON_REM1: R18.1, U11.P13 (SDA/NON_REM1)
HUB_NRESET: R15.1, U11.P15 (RESET_N)
HUB_RBIAS: R17.2, U11.P24 (RBIAS)
USB_CRFILT$: C13.1, U11.P10 (CRFILT)
USB_XTAL1$: C12.1, R16.2, U11.P22 (XTALIN), Y1.3
USB_XTAL2$: C11.1, R16.1, U11.P21 (XTALOUT), Y1.1
VBUS_DET_HUB: R14.2, U11.P16 (VBUS_DET)

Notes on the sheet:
USB2422 2-Port USB

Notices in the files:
parts and their libraries:
qualified_1: COMPANY_AND_YEAR: Geppetto, Gumstix Inc (c) 2019
